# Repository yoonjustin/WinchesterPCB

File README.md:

# WinchesterPCB
Open source JAMMA supergun project. KiCAD PCB design files, included are the symbols, footprints and BOM. 
The board is a two sided pcb with 1oz copper. Roughly 135mm x 86mm

# Design Breakdown

### Power
Power is supplied using a 20pin atx power connector. That way it can provide +5, -5 and +12v without having to deal with conversion on the pcb itself. In addition, it makes it easy to include a power switch and power led on the pcb. There is also logic in the atx power supply to cut power in the event of a short circuit. Which is a nice safety feature. 
  
The +5v power to the jamma connector needs to be pretty wide and beefy. If we assume 5A through a 1oz copper board thats about 5 inches, a 20 degree raise in temp puts us around 2.59mm trace width. I feel ok with the 2.5mm trace width on the board. Both the +5v and +12v are passing through an INA260 power monitoring IC. The INA260 can handle up to 36v and 15A, so its well within the use of this project. 

The teensy 4.1 uses 100mA, the oled screen 20mA, THS7376 30mA, FE1.1s 142mA, BA7230LS 50mA, and the MIC2026 is less than 1mA. So the total power consumption of the +5v coponents on the board is about 350mA. Using the .6mm trace with feels about right. 

I also made sure not to connect the +5v directly to the pins on the usb ports. The MIC2026-2YM will provide the usb ports with power according to the usb specifications. If anything goes out of spec, the MIC2026 will tell the FE1.1s usb hub to turn off the ports. This should help protect the board and the connected device, incase something goes wrong. 

### Component Video
Jamma arcade games were designed with outputting the video signal to an RGBS compatible display. And when it comes to home compatible tvs, component video is the closest to that signal. Composite video is a more common analog video input, but arcade games wont benefit from any kind of dithering effects.

The RGB signals are passed through individual potentimeters and sent to the BA7230LS to be converted to component signals. Those are then sent to a THS7376 video amplifier and connected to the sync signal which is cleaned up with an LM1881.

The THS7376 video amplifier is a drop in replacement for the THS7374. Either chip is supported in this design. Its worth noting that the 7374 uses much less power than the 7376, but Im not sure how the video quality is between the two. Im not sure if its my crt tv or my eyes, but I dont seem much different enabling and disabling the lowpass filter on the 7376.

### Teensy 4.1
The teensy 3.6 should also work for this design, but considering the 4.1 model is cheaper and faster, I dont see the point in using 3.6 unless you have one on hand. Due to the fact that the teensy 4.1 is not 5v tolerant, I have the pins connected to biased BJT transistors to connect the jamma pins to ground to signal a button press. The transistors have 1k resistors built in connecting the teensy io pin to the base and between the base and the emitter. One small design flaw is that the Player 1 Up signal is using pin 13 on the teensy, which is connected to an led. So every time player presses the up button the led lights up. I was hoping there would be a way to disable the led, but it is hard wired to the pin.

Be careful not to have the atx power and have the teensy plugged in with the onboard micro usb port at the same time. If you do want to have both plugged in and powered at the same time use this guide to do it safely https://www.pjrc.com/teensy/external_power.html. 

### PCB
There are in pad vias in this design. If assembling by hand its not a problem, but some machines do have problems with placing the correct amount of solder the pads with vias.

Both the front and back planes of the pcb are filled with ground. I also added vias along the outside for ground stitching. I dont think its that applicable for this project, but it doesnt hurt anything either. 

All of the connectors, power switch, power led, oled display and potentiometers are using through hole designs incase someone wants to put the board inside of a case. Wires could be ran to connectors on the side of a case. 

The expansion pins are using a footprint of a flat flex connector(SLW8R-5C7LF). A pcb could be mounted on top of the right side, there is another mounting hole near the LM1881 IC. 

### Future Design Considerations
The BA7230LS and FE1.1s are easy to use but not so easy to order and aquire. I have actually gotten some bad BA7230LS's from ebay and it would be nice to use a usb hub with better documentation for robust designs. I wish it had separate OVJ and enable lines for each port. This design from GGLABs converts rgb signals using OPAMPs and it might replace using the BA7230LS https://gglabs.us/sites/gglabs.us/files/a520hd_sch-A00.pdf. As for the usb hub, TI makes a wide variety of hubs but none are using the nice SSOP package.

There is an issue with PS3 controllers locking up the usbhub when connecting, that happens intermittantly. Its puzzling since ps4 and xbox one controllers do not exhibit this behavior. Retrocution sells a usb hub that also uses the FE1.1s and warns not to use pinheaders when connecting usb ports. I wonder if its a connection issue somehow. I also have an issue with using a Hori RAP N model fight stick. It connects for about a second and then disconnects. Either way, using a more modern usb hub from TI would be on the table for a board redesign. 

### Disclaimer
I did include the MIT license to this project, but to I would like to also state:

* I offer NO WARRANTY of any kind and assume NO RESPONSIBILITY for any potential damage caused by this device.
* You are free to build, use, sell, distribute as you like. Please credit and link this project if you are promoting this design

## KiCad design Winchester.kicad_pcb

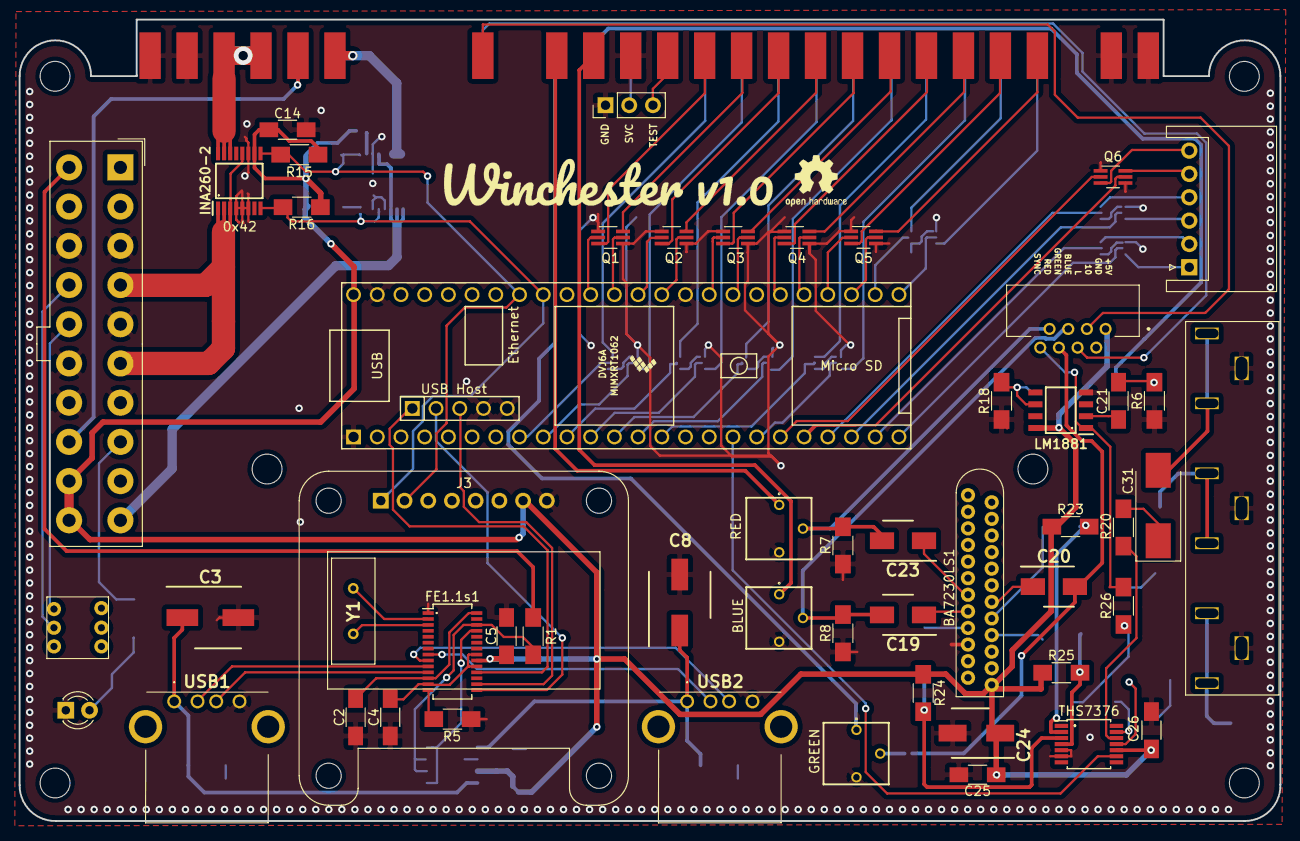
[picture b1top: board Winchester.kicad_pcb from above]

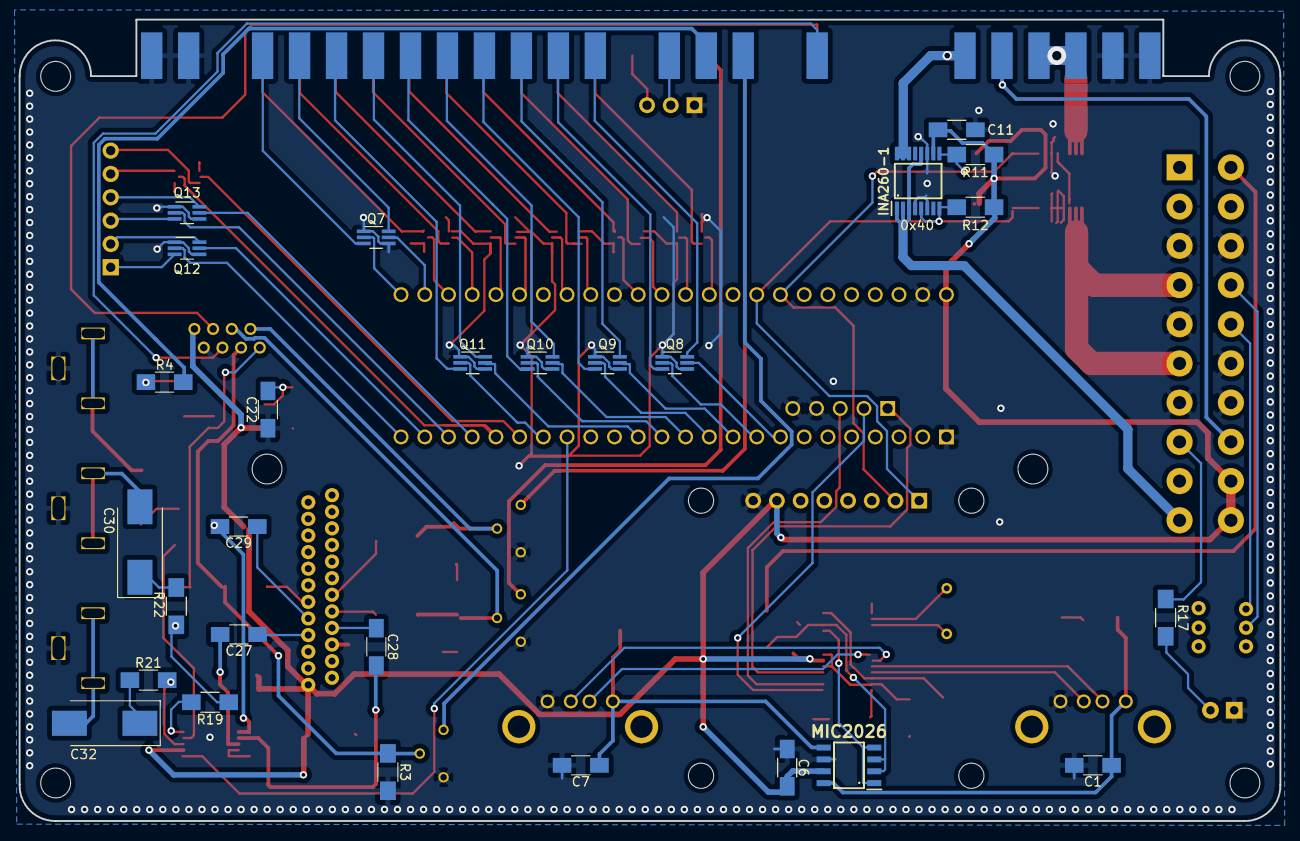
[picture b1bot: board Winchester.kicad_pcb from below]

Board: 2 copper layers, 135.1 x 85.8 mm, 89 parts (27 on the bottom side), 117 nets.

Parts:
ATX1: ATX20; Molex_MiniFit-JR-5556-20A_2x10x4.20mm_Straight
BA7230LS1: BA7230LS; szip24
B_POT1: R_POT_TRIM; 3362P_1
C1, C6, C7, C21, C22, C26, C27, C28, C29: 0.1uF; C_1206_HandSoldering
C2, C4, C5: 10uF; C_1206_HandSoldering
C3, C8: 220uF; EEE-1CA221XP
C11, C14: 1uF; C_1206_HandSoldering
C19, C20, C23: 1uF; EEE1HA010SR
C24: 10uF; EEE-1EA100SR
C25: 0.047uF; C_1206_HandSoldering
C30, C31, C32: 220uF; CP_Tantalum_Case-D_EIA-7343-31_Hand
COMPONENT1: PJRAN
D1: LED; LED_D3.0mm
FE1.1s1: FE1.1s; SSOP-28_3.9x9.9mm_Pitch0.635mm
G_POT1: R_POT_TRIM; 3362P_1
H1, H2, H3, H4, H5, H6: MountingHole; MountingHole_3.2mm_M3
INA260-1, INA260-2: INA260
J1: Conn_01x03_Female; Pin_Header_Straight_1x03_Pitch2.54mm
J2: SLW8R-5C7LF; SLW8R5C7LF
J3: SSD1306 OLED; Adafruit_SSD1306
KICK1: JST-XH; JST_XH_S06B-XH-A_06x2.50mm_Angled
L1: Logo; v1
LM1881: LM1881
LOGO1: Logo_Open_Hardware_Small; OSHW-Logo2_7.3x6mm_SilkScreen
MIC2026: MIC2026-2YM; SOIC127P599X173-8N
POWER1: SW_DPDT_x2; POWER_SW
Q1, Q2, Q3, Q4, Q5, Q6, Q7, Q8, Q9, Q10, Q11, Q12, Q13: MUN5230DW1T1G; SOT-363_SC-70-6_Handsoldering
R1, R11, R12, R15, R16: 10k; R_1206_HandSoldering
R3, R6, R7, R8: 390ohm; R_1206_HandSoldering
R4: 1Kohm; R_1206_HandSoldering
R5: 2.7k; R_1206_HandSoldering
R17: 330; R_1206_HandSoldering
R18: 680k; R_1206_HandSoldering
R19: 82ohm; R_1206_HandSoldering
R20: 56ohm; R_1206_HandSoldering
R21: 91ohm; R_1206_HandSoldering
R22: 75ohm; R_1206_HandSoldering
R23, R24, R25: 3.6Mohm; R_1206_HandSoldering
R26: 200ohm; R_1206_HandSoldering
R_POT1: R_POT_TRIM; 3362P_1
THS7376: THS7376; TSSOP-14_4.4x5mm_Pitch0.65mm
U1: Jamma; JAMMA56HALF
U7: Teensy4.1; Teensy41
USB1, USB2: USB_A; 875201010BLF
Y1: ECS120; ECS120184XCKM

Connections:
+3V3: ATX1.11, R1.1
+5V: ATX1.19, ATX1.20, BA7230LS1.24, C5.2, C6.2, C11.1, C14.1, C24.1, C25.1, C26.1, FE1.1s1.20, INA260-1.10, INA260-2.10, J2.1, J3.7, LM1881.8, MIC2026.7, R11.1, R12.1, R15.1, R16.1, R23.1, R24.1, R25.1, THS7376.10, U7.48
-5V: ATX1.18, U1.5, U1.E
/10: J2.3, U1.10
/+5VA: ATX1.4, ATX1.6, INA260-2.1, INA260-2.2, INA260-2.3, INA260-2.12
/+5VB: INA260-2.14, INA260-2.15, INA260-2.16, U1.3, U1.4, U1.C, U1.D
/+12VA: ATX1.10, INA260-1.1, INA260-1.2, INA260-1.3, INA260-1.12
/+12VB: INA260-1.14, INA260-1.15, INA260-1.16, U1.6, U1.F
/B: B_POT1.1, U1.13
/B-Y: C28.2, R24.2, THS7376.3
/BLUE: B_POT1.2, C19.2, J2.5, R8.2
/BYPASS: THS7376.9, U7.17
/CH1: C30.2, COMPONENT1.6, COMPONENT1.7
/CH2: C31.2, COMPONENT1.8, COMPONENT1.9
/CH3: C32.2, COMPONENT1.4, COMPONENT1.5
/COIN_P1: Q1.3, U1.16
/COIN_P2: Q8.6, U1.T
/CSYNC: J2.8, LM1881.1, R26.2
/DM: FE1.1s1.15, U7.56
/DM1: FE1.1s1.10, USB1.2
/DM2: FE1.1s1.8, USB2.2
/DP: FE1.1s1.16, U7.57
/DP1: FE1.1s1.11, USB1.3
/DP2: FE1.1s1.9, USB2.3
/ENP: FE1.1s1.25, MIC2026.1, MIC2026.4
/G: G_POT1.1, U1.N
/GREEN: C20.2, G_POT1.2, J2.6, R3.1
/L: J2.4, U1.L
/OVCJ: FE1.1s1.26, MIC2026.2, MIC2026.3, R1.2
/P1_B1: Q4.3, U1.22
/P1_B1_29: Q4.5, U7.29
/P1_B2: Q4.6, U1.23
/P1_B2_30: Q4.2, U7.30
/P1_B3: Q5.3, U1.24
/P1_B3_27: Q5.5, U7.27
/P1_B4: KICK1.1, Q12.3
/P1_B4_23: Q12.5, U7.23
/P1_B4_28: Q5.2, U7.28
/P1_B4_N: Q5.6, U1.25
/P1_B5: KICK1.3, Q13.3
/P1_B5_21: Q13.5, U7.21
/P1_B6: KICK1.5, Q6.6
/P1_B6_19: Q6.2, U7.19
/P1_COIN_37: Q1.5, U7.37
/P1_DOWN: Q2.6, U1.19
/P1_DOWN_36: Q2.2, U7.36
/P1_LEFT: Q3.3, U1.20
/P1_LEFT_32: Q3.5, U7.32
/P1_RIGHT: Q3.6, U1.21
/P1_RIGHT_33: Q3.2, U7.33
/P1_START: Q1.6, U1.17
/P1_START_38: Q1.2, U7.38
/P1_UP: Q2.3, U1.18
/P1_UP_35: Q2.5, U7.35
/P2_B1: Q11.6, U1.Z
/P2_B1_18: Q11.2, U7.18
/P2_B2: Q11.3, U1._a
/P2_B2_14: Q11.5, U7.14
/P2_B3: Q7.6, U1._b
/P2_B3_25: Q7.2, U7.25
/P2_B4: KICK1.2, Q12.6
/P2_B4_24: Q12.2, U7.24
/P2_B4_26: Q7.5, U7.26
/P2_B4_N: Q7.3, U1._c
/P2_B5: KICK1.4, Q13.6
/P2_B5_22: Q13.2, U7.22
/P2_B6: KICK1.6, Q6.3
/P2_B6_20: Q6.5, U7.20
/P2_COIN_9: Q8.2, U7.9
/P2_DOWN: Q9.3, U1.W
/P2_DOWN_10: Q9.5, U7.10
/P2_LEFT: Q10.6, U1.X
/P2_LEFT_13: Q10.2, U7.13
/P2_RIGHT: Q10.3, U1.Y
/P2_RIGHT_12: Q10.5, U7.12
/P2_START: Q8.3, U1.U
/P2_START_8: Q8.5, U7.8
/P2_UP: Q9.6, U1.V
/P2_UP_11: Q9.2, U7.11
/R: R_POT1.1, U1.12
/R-Y: C27.2, R25.2, THS7376.4
/RED: C23.2, J2.7, R7.2, R_POT1.2
/S: R4.2, U1.P
/SCL: INA260-1.9, INA260-2.9, J3.2, R11.2, R15.2, U7.41
/SDA: INA260-1.5, INA260-1.8, INA260-2.8, J3.1, R12.2, R16.2, U7.40
/SERVICE: J1.2, U1.R
/SYNC: C21.2, R4.1, R6.2
/TEST: J1.3, U1.15
/USBA5V: C1.1, C3.1, MIC2026.8, USB1.1
/USBB5V: C7.1, C8.1, MIC2026.5, USB2.1
/USBVCC: FE1.1s1.18, U7.55
/Y: C29.2, R23.2, THS7376.2
GND: ATX1.3, ATX1.5, ATX1.7, ATX1.13, ATX1.16, ATX1.17, BA7230LS1.19, B_POT1.3, C1.2, C2.1, C3.2, C4.1, C5.1, C6.1, C7.2, C8.2, C11.2, C14.2, C22.1, C24.2, C25.2, C26.2, COMPONENT1.1, COMPONENT1.2, COMPONENT1.3, D1.1, FE1.1s1.1, G_POT1.3, INA260-1.4, INA260-1.6, INA260-1.11, INA260-2.4, INA260-2.5, INA260-2.6, INA260-2.11, J1.1, J2.2, J3.8, LM1881.4, MIC2026.6, Q1.1, Q1.4, Q2.1, Q2.4, Q3.1, Q3.4, Q4.1, Q4.4, Q5.1, Q5.4, Q6.1, Q6.4, Q7.1, Q7.4, Q8.1, Q8.4, Q9.1, Q9.4, Q10.1, Q10.4, Q11.1, Q11.4, Q12.1, Q12.4, Q13.1, Q13.4, R3.2, R5.2, R6.1, R7.1, R8.1, R18.1, R_POT1.3, THS7376.5, THS7376.6, U1.1, U1.2, U1.14, U1.27, U1.28, U1.A, U1.B, U1._e, U1._f, U7.1, U7.34, U7.47, U7.58, U7.59, USB1.4, USB2.4
unnamed: ATX1.8, R17.1
unnamed: ATX1.14, POWER1.3
unnamed: ATX1.15, POWER1.1
unnamed: BA7230LS1.13, C23.1
unnamed: BA7230LS1.14, C20.1
unnamed: BA7230LS1.15, C19.1
unnamed: BA7230LS1.16, C29.1
unnamed: BA7230LS1.17, C28.1
unnamed: BA7230LS1.18, C27.1
unnamed: C2.2, FE1.1s1.12, FE1.1s1.28
unnamed: C4.2, FE1.1s1.13, FE1.1s1.19, FE1.1s1.21
unnamed: C21.1, LM1881.2
unnamed: C22.2, LM1881.6, R18.2
unnamed: C30.1, R22.1
unnamed: C31.1, R20.1
unnamed: C32.1, R21.1
unnamed: D1.2, R17.2
unnamed: FE1.1s1.2, Y1.2
unnamed: FE1.1s1.3, Y1.1
unnamed: FE1.1s1.14, R5.1
unnamed: R19.1, R22.2, R26.1
unnamed: R19.2, THS7376.13
unnamed: R20.2, THS7376.12
unnamed: R21.2, THS7376.11
